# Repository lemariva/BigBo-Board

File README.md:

# BigBo-Board

BigBo is a multi-target board for Energy Metering & Power Monitoring. It's the big brother of [PiCoBo](https://github.com/lemariva/PiCoBo-Board). I designed it using the MSP430F5529LP that is part of the MSP430 Texas Instruments family of low-power microcontrollers.

More info will be available on https://lemariva.com soon.

## Components
The board includes:
* CP2102 for UART communication (with ESD-Protection)
* Socket for a NRF24L01 module
* CD4504B: level shifter
* BQ27510-Q3: battery fuel gauge
* BQ24210DQCT: Li-Ion battery charger
* CAT24FC32UI: EEPROM memory
* TPS6300x: buck-boost converters (for 5V)
* MCP39F501: power-monitoring
* etc.

This board is a Energy Metering & Power Monitoring demonstration board with communication possibilities (0.1% error across 4000:1 dynamic range). I designed it near 2013, when home solutions were limited and expensive. The power energy metering & power monitoring functions are based on the [ARD00455](https://www.microchip.com/Developmenttools/ProductDetails/ARD00455) board.

The board can be supplied using:
* a battery (Li-Ion) which can be also charged
* 5V over the micro-usb connector
* 230V AC (not a typo error - 230V AC!). The floating 3.3V is generated using a LM1117. Check the HIGH-Voltage page on the schematic.

Additionally multiple pinouts are available to connect external sensors (e.g. DHT11), servo motors, LEDs etc. For testing uses it can be programmed using the MSP430F5529LP LaunchPad.

## PCB
|||
|:- |:-|

### Applications
* Energy Metering & Power Monitoring
* Smart switch
* Sensor measurement (Temperature etc.)
* LEDs control
* Communication
* etc.

### Revision
* 1.0 first version

### Disclaimer
Use at your own risk and be careful specially with the 230V AC part.

I ordered the board (I have 10 PCBs over here) but I didn't have enough time to solder the components. I've checked the design many times but errors could be over there. I'll be updating the code that I had for the board soon.

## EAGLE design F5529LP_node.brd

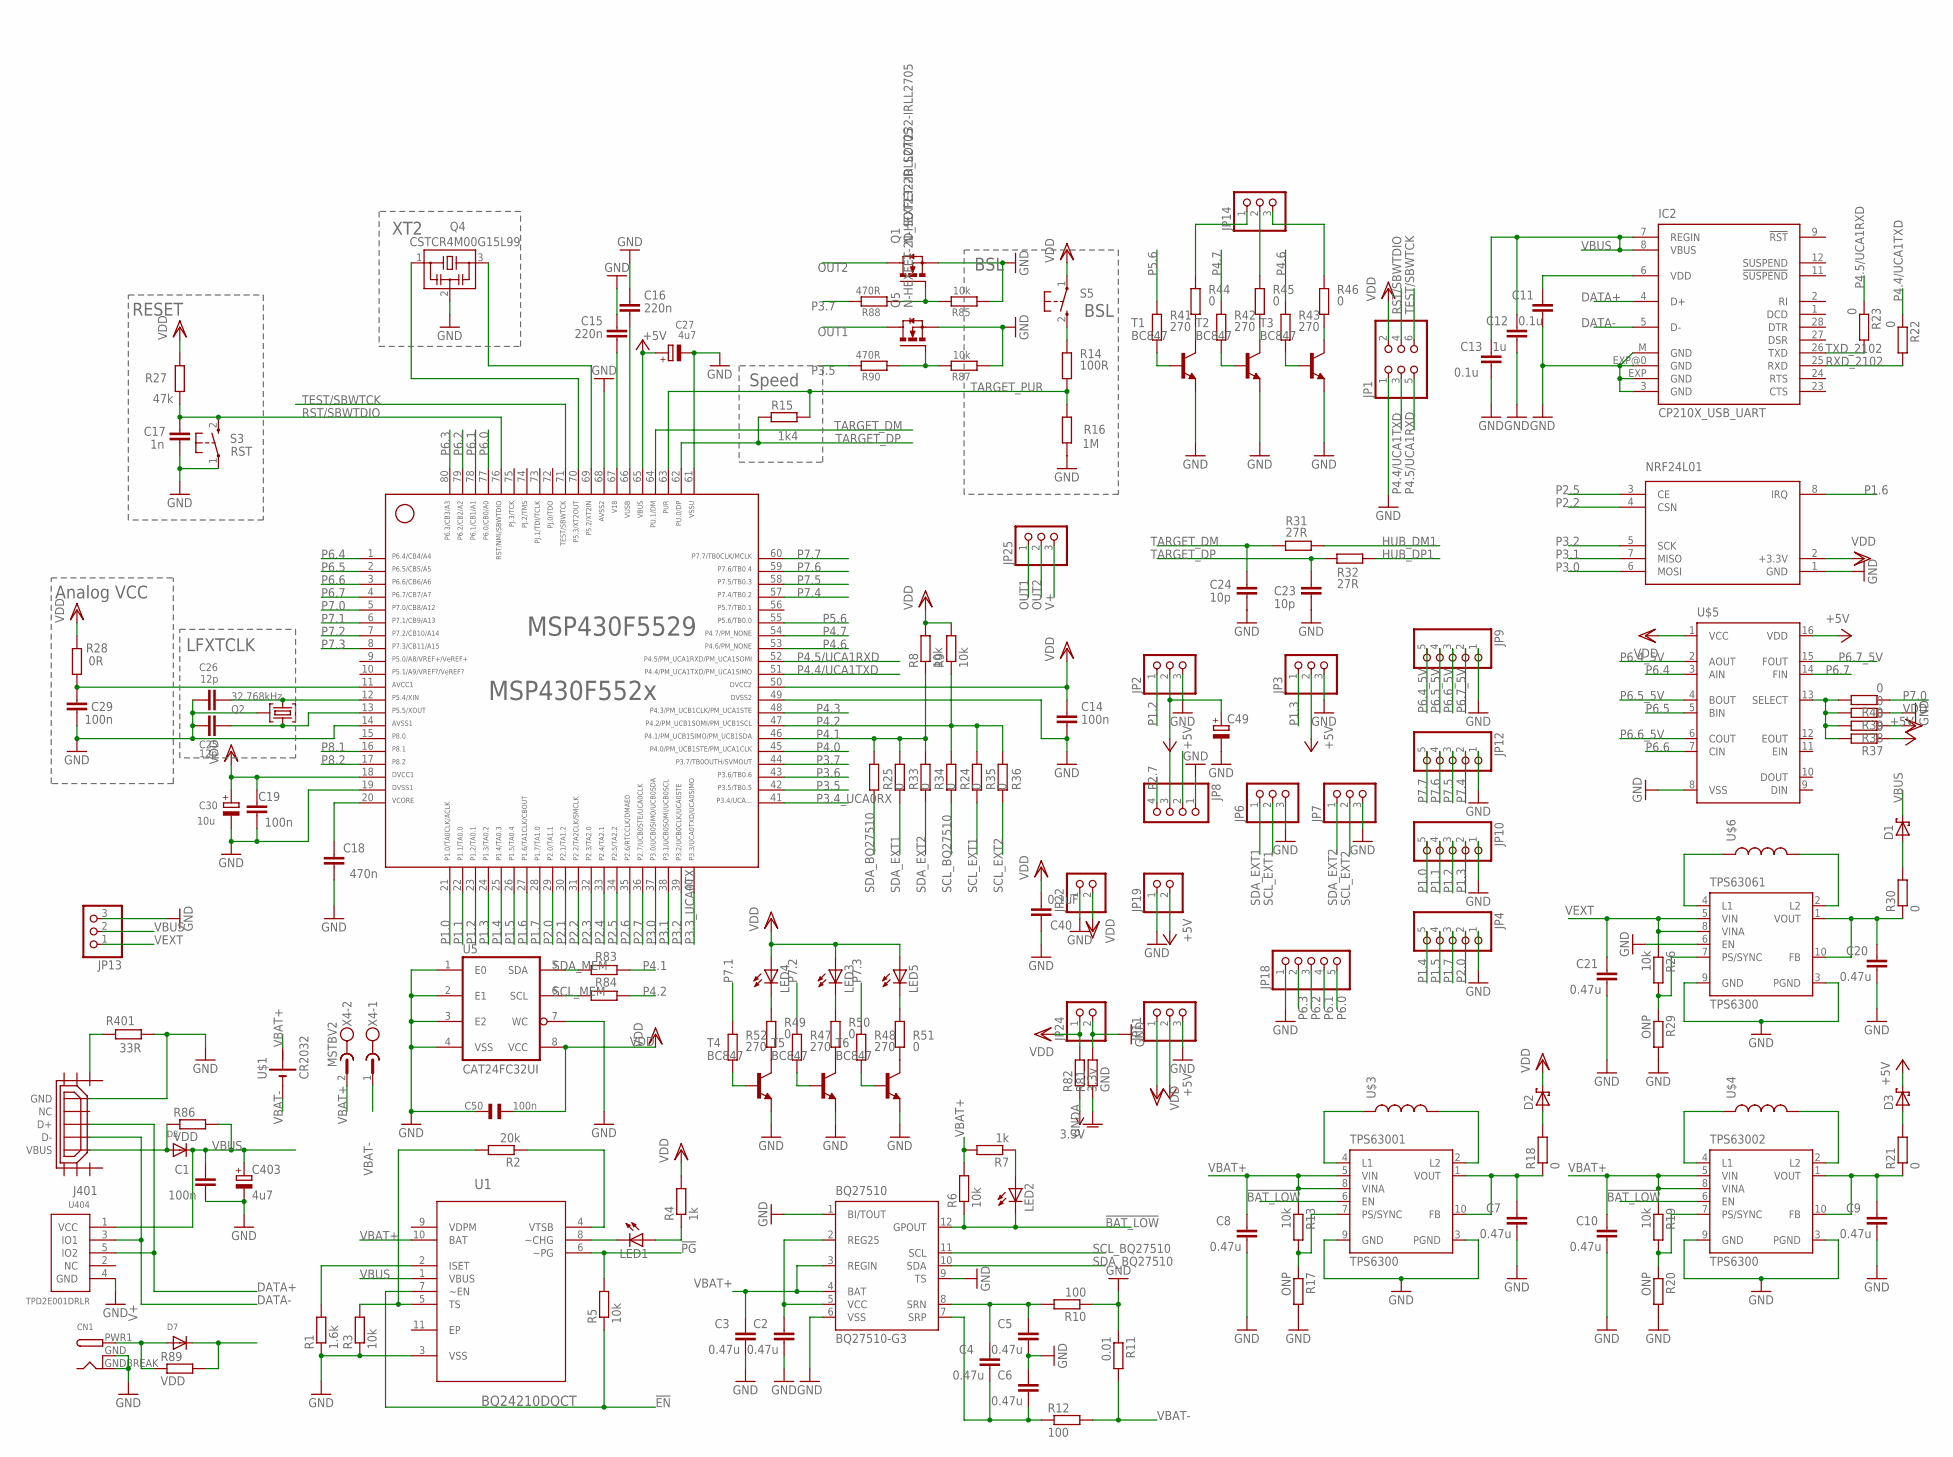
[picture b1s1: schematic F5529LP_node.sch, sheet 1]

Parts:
BQ27510: BQ27510-G3; DRZ
C1, C14, C19, C29: 100n; C0603
C2, C3, C4, C5, C6, C7, C8, C9, C10, C20, C21: 0.47u; C0603
C11, C13: 0.1u; C0603
C12: 1u; C0603
C15, C16: 220n; C0603
C17: 1n; C0603
C18: 470n; C0603
C23, C24: 10p; C0603
C25, C26: 12p; C0603
C27, C403: 4u7; A/3216-18R
C30: 10u; A/3216-18R
C40: 0.1uF; C0603
C49: CPOL-EUF; PANASONIC_F
C50: 100n; 0402
CN1: DCBARRELSMT; DCJACK_2MM_SMT
D1, D2, D3: SCHOTTKY-DIODE; DIODE_SMB
D7, D8: DIODESOT23_REFLOW; SOT23-R
IC2: CP210X_USB_UART; MLP28
J401: USB_MICRO_FLIPPED; HIROSE-ZX62R-B-5P
JP1: PINHD-2X3; 2X03
JP2, JP3, JP25: PINHD-1X3; 1X03
JP4, JP9, JP10, JP12, JP18: PINHD-1X5_2.00; 1X05M
JP6, JP7, JP11, JP13, JP14: PINHD-1X3_2.00; 1X03M
JP8: PINHD-1X4_2.00; 1X04M
JP19, JP22, JP24: PINHD-1X2_2.00; 1X02M
LED1, LED2, LED3, LED4, LED5: LEDSML0805; SML0805
MSP430F5529: MSP430F5529IPNR; PN80
NRF24L01: NRF24L01HP; NRF24L01_HP
Q1, Q5: N-HEXFET-2D_SOT232-IRLL2705; SOT223
Q2: 32.768kHz; MS3V-T1R
Q4: CSTCR4M00G15L99; MURATA-FILTER_CSTCR
R1: 1.6k; R0603
R2: 20k; R0603
R3, R5, R6, R8, R9, R13, R19, R26: 10k; R0603
R4, R7: 1k; R0603
R10, R12: 100; R0603
R11: 0.01; R0603
R14: 100R; R0603
R15: 1k4; R0603
R16: 1M; R0603
R17, R20, R29: ONP; R0603
R18, R21, R22, R23, R30, R37, R38, R39, R40, R44, R45, R46, R49, R50, R51: 0; R0603
R24, R25, R33, R34, R35, R36, R83, R84: 0; R0201
R27: 47k; R0603
R28: 0R; R0603
R31, R32: 27R; R0603
R41, R42, R43, R47, R48, R52: 270; R0603
R81: GND; R0402
R82: 3.3v; R0402
R85, R87: 10k; 0603
R86, R89: VDD; R0201
R88, R90: 470R; 0603
R401: 33R; R0603
S3: RST; PBTH
S5: BSL; PBTH
T1, T2, T3, T4, T5, T6: BC847; SOT23
TPS63001, TPS63002, TPS63061: TPS6300; DRC-S-PVSON-N10
U1: BQ24210DQCT; SON50P200X300X80-11N
U5: CAT24FC32UI; TSSOP8
U404: TPD2E001DRLR; TPD2E001-DRL
U$1: CR2032
U$3, U$4, U$6: INDUCTOR-B82462G; B82462G
U$5: CD4504B; SOIC16
X4: MSTBV2

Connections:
3.3V: R82.1; also elsewhere on the board
!BAT_LOW: BQ27510.12 (GPOUT), LED2.C, R6.1, TPS63001.6 (EN), TPS63002.6 (EN)
!EN: R5.1, U1.7 (~EN)
!PG: R5.2, U1.6 (~PG)
+5V: C27.+, C49.+, D3.C (A), JP2.2, JP3.2, JP11.2, JP19.2, MSP430F5529.65, R37.1, U$5.16 (VDD); also elsewhere on the board
AVCC: C29.1, MSP430F5529.11, R28.1
DATA+: IC2.4 (D+), J401.D+, U404.5 (IO2)
DATA-: IC2.5 (D-), J401.D-, U404.3 (IO1)
GND: BQ27510.1 (BI/TOUT), BQ27510.6 (VSS), BQ27510.9 (TS), C1.2, C2.2, C3.2, C5.2, C6.1, C7.2, C8.2, C9.2, C10.2, C11.2, C12.2, C13.2, C14.2, C15.2, C16.2, C17.2, C18.1, C19.1, C20.2, C21.2, C23.2, C24.2, C25.1, C26.1, C27.-, C29.2, C30.-, C40.1, C49.-, C50.2, C403.-, CN1.GND (GNDBREAK), CN1.GNDBREAK (GND), IC2.3 (GND), IC2.EXP (GND), IC2.EXP@0 (GND), IC2.M (GND), J401.GND, JP1.1, JP2.3, JP3.3, JP4.1, JP6.3, JP7.3, JP8.1, JP9.1, JP10.1, JP11.3, JP12.1, JP13.3, JP18.1, JP19.1, JP22.1, JP24.2, MSP430F5529.14, MSP430F5529.19, MSP430F5529.49, MSP430F5529.61, MSP430F5529.68, NRF24L01.1 (GND), Q1.3 (S), Q2.P3 (GND), Q4.2, Q5.3 (S), R1.1, R3.1, R10.1, R11.1, R16.1, R17.2, R20.2, R29.2, R39.1, R81.2, R85.1, R87.1, R401.2, S3.1, T1.2 (E), T2.2 (E), T3.2 (E), T4.2 (E), T5.2 (E), T6.2 (E), TPS63001.3 (PGND), TPS63001.9 (GND), TPS63002.3 (PGND), TPS63002.9 (GND), TPS63061.3 (PGND), TPS63061.6 (EN), TPS63061.9 (GND), U1.3 (VSS), U5.1 (E0), U5.2 (E1), U5.3 (E2), U5.4 (VSS), U5.7 (WC), U404.4 (GND), U$5.8 (VSS); also elsewhere on the board
GNDA: R81.1; also elsewhere on the board
HUB_DM1: R31.1
HUB_DP1: R32.1
unnamed: R1.2, U1.2 (ISET)
unnamed: R2.1, U1.4 (VTSB)
unnamed: R2.2, R3.2, U1.5 (TS)
unnamed: R14.1, S5.2 (S)
unnamed: LED1.C, U1.8 (~CHG)
unnamed: LED1.A, R4.1
unnamed: BQ27510.2 (REG25), BQ27510.5 (VCC), C2.1
unnamed: TPS63002.4 (L1), U$4.P$1 (1)
unnamed: LED2.A, R7.1
unnamed: J401.SHIELD1, R401.1
unnamed: BQ27510.8 (SRN), C4.1, C5.1, R10.2
unnamed: TPS63001.4 (L1), U$3.P$1 (1)
unnamed: TPS63001.2 (L2), U$3.P$2 (2)
unnamed: BQ27510.7 (SRP), C4.2, C6.2, R12.1
unnamed: TPS63002.2 (L2), U$4.P$2 (2)
unnamed: R13.2, R17.1, TPS63001.7 (PS/SYNC)
unnamed: R19.2, R20.1, TPS63002.7 (PS/SYNC)
unnamed: C9.1, R21.1, TPS63002.1 (VOUT), TPS63002.10 (FB)
unnamed: C7.1, R18.1, TPS63001.1 (VOUT), TPS63001.10 (FB)
unnamed: C11.1, IC2.6 (VDD)
unnamed: TPS63061.4 (L1), U$6.P$1 (1)
unnamed: TPS63061.2 (L2), U$6.P$2 (2)
unnamed: R26.2, R29.1, TPS63061.7 (PS/SYNC)
unnamed: C20.1, R30.1, TPS63061.1 (VOUT), TPS63061.10 (FB)
unnamed: R37.2, R38.2, R39.2, R40.2, U$5.13 (SELECT)
unnamed: R41.2, T1.1 (B)
unnamed: R42.2, T2.1 (B)
unnamed: R43.2, T3.1 (B)
unnamed: R46.2, T3.3 (C)
unnamed: JP14.1, R44.1
unnamed: JP14.2, R45.1
unnamed: JP14.3, R46.1
unnamed: R44.2, T1.3 (C)
unnamed: R45.2, T2.3 (C)
unnamed: D1.A (C), R30.2
unnamed: D2.A (C), R18.2
unnamed: D3.A (C), R21.2
unnamed: R47.2, T5.1 (B)
unnamed: R48.2, T6.1 (B)
unnamed: R51.2, T6.3 (C)
unnamed: LED4.C, R49.1
unnamed: LED3.C, R50.1
unnamed: LED5.C, R51.1
unnamed: R49.2, T4.3 (C)
unnamed: R50.2, T5.3 (C)
unnamed: R52.2, T4.1 (B)
unnamed: Q1.1 (G), R85.2, R88.1
unnamed: D8.1 (A), J401.VBUS, R86.1
unnamed: Q5.1 (G), R87.2, R90.1
OUT1: JP25.1, Q5.2 (D), Q5.4 (D)
OUT2: JP25.2, Q1.2 (D), Q1.4 (D)
P1.0: JP10.5, MSP430F5529.21
P1.1: JP10.4, MSP430F5529.22
P1.2: JP2.1, JP10.3, MSP430F5529.23
P1.3: JP3.1, JP10.2, MSP430F5529.24
P1.4: JP4.5, MSP430F5529.25
P1.5: JP4.4, MSP430F5529.26
P1.6: MSP430F5529.27, NRF24L01.8 (IRQ)
P1.7: JP4.3, MSP430F5529.28
P2.0: JP4.2, MSP430F5529.29
P2.1: MSP430F5529.30
P2.2: MSP430F5529.31, NRF24L01.4 (CSN)
P2.3: MSP430F5529.32
P2.4: MSP430F5529.33
P2.5: MSP430F5529.34, NRF24L01.3 (CE)
P2.6: MSP430F5529.35
P2.7: JP8.4, MSP430F5529.36; also elsewhere on the board
P3.0: MSP430F5529.37, NRF24L01.6 (MOSI)
P3.1: MSP430F5529.38, NRF24L01.7 (MISO)
P3.2: MSP430F5529.39, NRF24L01.5 (SCK)
P3.3_UCA0TX: JP8.2, MSP430F5529.40; also elsewhere on the board
P3.4_UCA0RX: JP8.3, MSP430F5529.41; also elsewhere on the board
P3.5: MSP430F5529.42, R90.2
P3.6: MSP430F5529.43
P3.7: MSP430F5529.44, R88.2
P4.0: MSP430F5529.45
P4.1: MSP430F5529.46, R8.1, R25.1, R33.1, R34.1, R83.2
P4.2: MSP430F5529.47, R9.1, R24.1, R35.1, R36.1, R84.2
P4.3: MSP430F5529.48
P4.4/UCA1TXD: JP1.3, MSP430F5529.51, R22.1
P4.5/UCA1RXD: JP1.5, MSP430F5529.52, R23.1
P4.6: MSP430F5529.53, R43.1
P4.7: MSP430F5529.54, R42.1
P5.2/XT2IN: MSP430F5529.69, Q4.3
P5.3/XT2OUT: MSP430F5529.70, Q4.1
P5.4/XIN: C26.2, MSP430F5529.12, Q2.P2 (2)
P5.5/XOUT: C25.2, MSP430F5529.13, Q2.P1 (1)
P5.6: MSP430F5529.55, R41.1
P6.0: JP18.5, MSP430F5529.77
P6.1: JP18.4, MSP430F5529.78
P6.2: JP18.3, MSP430F5529.79
P6.3: JP18.2, MSP430F5529.80
P6.4: MSP430F5529.1, U$5.3 (AIN)
P6.4_5V: JP9.5, U$5.2 (AOUT)
P6.5: MSP430F5529.2, U$5.5 (BIN)
P6.5_5V: JP9.4, U$5.4 (BOUT)
P6.6: MSP430F5529.3, U$5.7 (CIN)
P6.6_5V: JP9.3, U$5.6 (COUT)
P6.7: MSP430F5529.4, U$5.14 (FIN)
P6.7_5V: JP9.2, U$5.15 (FOUT)
P7.0: MSP430F5529.5, R40.1
P7.1: MSP430F5529.6, R52.1
P7.2: MSP430F5529.7, R47.1
P7.3: MSP430F5529.8, R48.1
P7.4: JP12.2, MSP430F5529.57
P7.5: JP12.3, MSP430F5529.58
P7.6: JP12.4, MSP430F5529.59
P7.7: JP12.5, MSP430F5529.60
P8.1: MSP430F5529.16
P8.2: MSP430F5529.17
PWPD: BQ27510.EXP@1 (PWPD), BQ27510.EXP@2 (PWPD), BQ27510.EXP@3 (PWPD), BQ27510.EXP@4 (PWPD), BQ27510.EXP@5 (PWPD), BQ27510.EXP@6 (PWPD), BQ27510.EXP@7 (PWPD), BQ27510.EXP@8 (PWPD), BQ27510.EXP@9 (PWPD)
RST/SBWTDIO: C17.1, JP1.4, MSP430F5529.76, R27.1, S3.2 (S)
RXD_2102: IC2.25 (RXD), R22.2
SCL_BQ27510: BQ27510.11 (SCL), R24.2
SCL_EXT1: JP6.2, R35.2
SCL_EXT2: JP7.2, R36.2
SCL_MEM: R84.1, U5.6 (SCL)
SDA_BQ27510: BQ27510.10 (SDA), R25.2
SDA_EXT1: JP6.1, R33.2
SDA_EXT2: JP7.1, R34.2
SDA_MEM: R83.1, U5.5 (SDA)
TARGET_DM: C24.1, MSP430F5529.64, R31.2
TARGET_DP: C23.1, MSP430F5529.62, R15.2, R32.2
TARGET_PUR: MSP430F5529.63, R14.2, R15.1, R16.2
TARGET_VUSB: C16.1, MSP430F5529.66
TEST/SBWTCK: JP1.6, MSP430F5529.71
TXD_2102: IC2.26 (TXD), R23.2
V18: C15.1, MSP430F5529.67
V+: CN1.PWR1 (PWR), D7.1 (A), JP25.3, R89.1
VBAT+: BQ27510.3 (REGIN), BQ27510.4 (BAT), C3.1, C8.1, C10.1, R6.2, R7.2, R13.1, R19.1, TPS63001.5 (VIN), TPS63001.8 (VINA), TPS63002.5 (VIN), TPS63002.8 (VINA), U1.10 (BAT), U$1.P$1 (+), X4.2
VBAT-: R11.2, R12.2, U$1.P$2 (-), X4.1
VBUS: C1.1, C12.1, C13.1, C403.+, D1.C (A), D7.3 (C), D8.3 (C), IC2.7 (REGIN), IC2.8 (VBUS), JP13.2, R86.2, R89.2, U1.1 (VBUS), U404.1 (VCC)
VCORE: C18.2, MSP430F5529.20
VDD: C14.1, C19.2, C30.+, C40.2, C50.1, D2.C (A), JP1.2, JP11.1, JP22.2, JP24.1, LED3.A, LED4.A, LED5.A, MSP430F5529.18, MSP430F5529.50, NRF24L01.2 (+3.3V), R4.2, R8.2, R9.2, R27.2, R28.2, R38.1, R82.2, S5.1, U5.8 (VCC), U$5.1 (VCC); also elsewhere on the board
VEXT: C21.1, JP13.1, R26.1, TPS63061.5 (VIN), TPS63061.8 (VINA)

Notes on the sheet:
RESET
LFXTCLK
XT2
BSL
Speed
Analog VCC

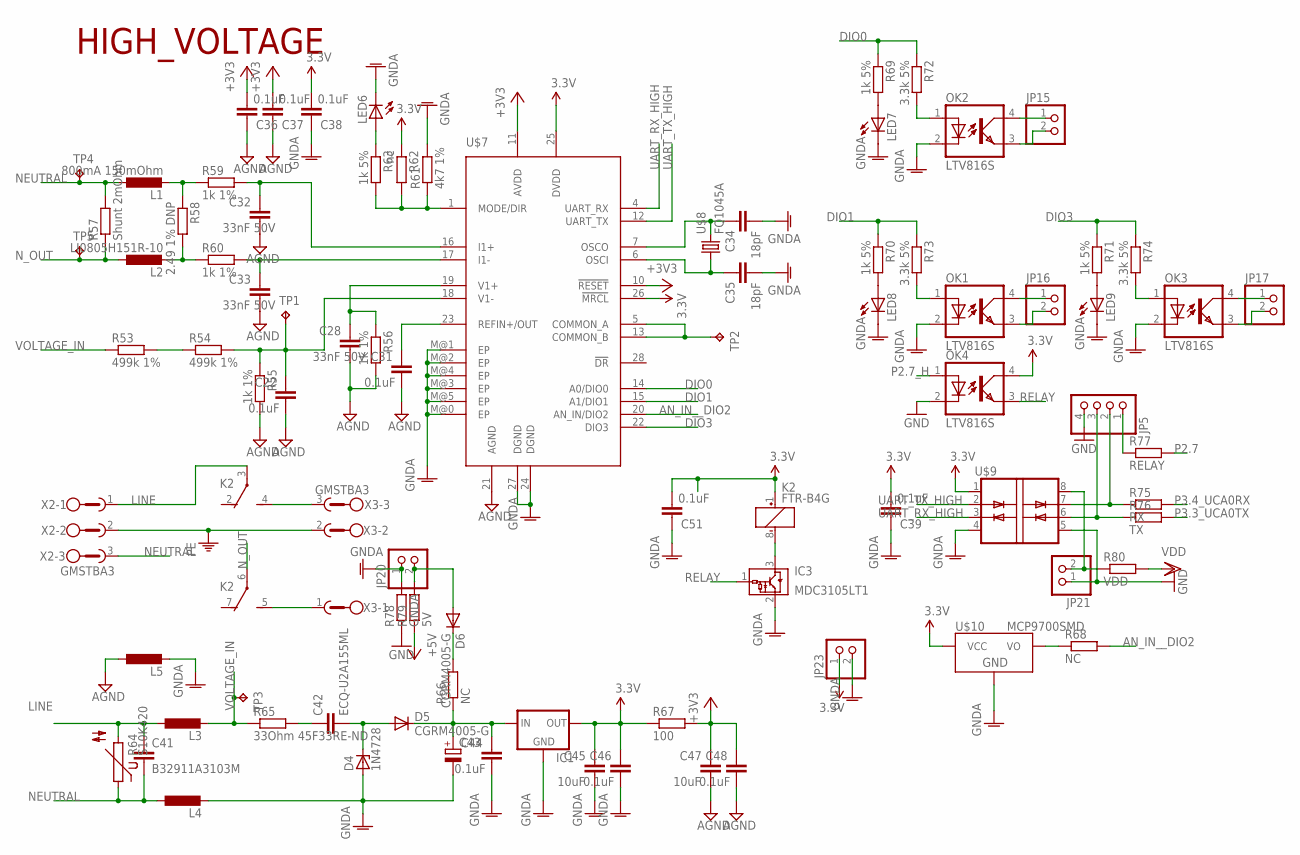
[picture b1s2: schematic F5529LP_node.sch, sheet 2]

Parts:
C22, C31, C36, C37, C38, C39, C44, C46, C48: 0.1uF; C0603
C28, C32, C33: 33nF 50V; C0603
C34, C35: 18pF; C0603
C41: B32911A3103M; C075-042X103
C42: ECQ-U2A155ML; C275-173X316
C43: CPOL-EUF; PANASONIC_F
C45, C47: 10uF; C1206
C51: 0.1uF; C0805
D4: 1N4728; DO41Z10
D5, D6: CGRM4005-G; SOD-123_MINI-SMA
IC1: LM1117; SOT223
IC3: MDC3105LT1; SOT23
JP5: PINHD-1X4_2.00; 1X04M
JP15, JP16, JP17, JP20, JP21, JP23: PINHD-1X2_2.00; 1X02M
K2: FTR-B4G
L1: 800mA 150mOhm; L2825P
L2: LI0805H151R-10; L2825P
L3, L4: L-EU0207/5V; 0207/5V
L5: L-EUL2825P; L2825P
LED6, LED7, LED8, LED9: LEDCHIPLED_0805; CHIPLED_0805
OK1, OK2, OK3, OK4: LTV816S; SMD4
R53, R54: 499k 1%; R2010
R55, R56, R59, R60: 1k 1%; R0603
R57: Shunt 2mOhm; R2512
R58: 2.49 1% DNP; R0603
R61: 4k7 1%; R0603
R62: nc; R0603
R63, R69, R70, R71: 1k 5%; R0603
R64: S10K420
R65: 33Ohm 45F33RE-ND; 0617V
R66: NC; R2010
R67: 100; R0603
R68: NC; R0603
R72, R73, R74: 3.3k 5%; R0603
R75: RX; R0201
R76: TX; R0201
R77: RELAY; R0201
R78: GNDA; R0402
R79: 5V; R0402
R80: VDD; R0201
TP1, TP3, TP4, TP5: TPB2,54; B2,54
TP2: TPB1,27; B1,27
U$7: MCP39F501; QFN28
U$8: FQ1045A
U$9: IL712; SOIC08
U$10: MCP9700SMD; SOT23-3
U$11: HIGH_VOLTAGE
X2, X3: GMSTBA3

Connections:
3.3V: C38.2, C39.2, C45.1, C46.1, C51.2, IC1.2 (OUT), JP23.1, K2.1 (+), OK4.4 (COL), R62.1, R67.1, U$7.25 (DVDD), U$7.26 (!MRCL), U$9.1 (VDD1), U$10.1 (VCC); also elsewhere on the board
!DR: U$7.28 (!DR)
+3V3: C36.2, C37.2, C47.1, C48.1, R67.2, U$7.10 (!RESET), U$7.11 (AVDD)
+5V: R79.1; also elsewhere on the board
AGND: C22.2, C28.2, C31.2, C32.2, C33.2, C36.1, C37.1, C47.2, C48.2, L5.1, R55.2, R56.2, U$7.21 (AGND)
AN_IN__DIO2: R68.2, U$7.20 (AN_IN/DIO2)
DIO0: R69.1, R72.1, U$7.14 (A0/DIO0)
DIO1: R70.1, R73.1, U$7.15 (A1/DIO1)
DIO3: R71.1, R74.1, U$7.22 (DIO3)
GND: JP5.4, JP21.1, OK4.2 (C), R78.1, U$9.5 (GND2); also elsewhere on the board
GNDA: C34.2, C35.2, C38.1, C39.1, C43.-, C44.2, C45.2, C46.2, C51.1, D4.A, IC1.1 (GND), IC3.2 (GND), JP20.1, JP23.2, L4.2, L5.2, LED6.C, LED7.C, LED8.C, LED9.C, OK1.2 (C), OK2.2 (C), OK3.2 (C), R61.2, R78.2, U$7.24 (DGND), U$7.27 (DGND), U$7.M@0 (EP), U$7.M@1 (EP), U$7.M@2 (EP), U$7.M@3 (EP), U$7.M@4 (EP), U$7.M@5 (EP), U$9.4 (GND1), U$10.3 (GND); also elsewhere on the board
LINE: C41.1, K2.3, L3.1, R64.2, X2.1
LINE_RELAY: K2.4 (S), X3.3
unnamed: LED8.A, R70.2
unnamed: R53.2, R54.1
unnamed: C22.1, R54.2, R55.1, TP1.TP, U$7.18 (V1-)
unnamed: C28.1, R56.1, U$7.19 (V1+)
unnamed: C31.1, U$7.23 (REFIN+/OUT)
unnamed: LED7.A, R69.2
unnamed: LED9.A, R71.2
unnamed: L1.2, R58.1, R59.1
unnamed: L2.2, R58.2, R60.1
unnamed: C33.1, R60.2, U$7.17 (I1-)
unnamed: C32.1, R59.2, U$7.16 (I1+)
unnamed: R61.1, R62.2, R63.2, U$7.1 (MODE/DIR)
unnamed: LED6.A, R63.1
unnamed: C34.1, U$7.7 (OSCO), U$8.2 (3)
unnamed: C35.1, U$7.6 (OSCI), U$8.1
unnamed: C43.+, C44.1, D5.C, IC1.3 (IN), R66.1
unnamed: D6.C, R66.2
unnamed: OK2.1 (A), R72.2
unnamed: TP2.TP, U$7.5 (COMMON_A), U$7.13 (COMMON_B)
unnamed: R68.1, U$10.2 (VO)
unnamed: C42.2, D4.C, D5.A
unnamed: C42.1, R65.2
unnamed: OK1.1 (A), R73.2
unnamed: OK3.1 (A), R74.2
unnamed: JP5.2, R75.1, U$9.7 (OUT1)
unnamed: JP5.3, R76.1, U$9.6 (IN2)
unnamed: JP15.1, OK2.4 (COL)
unnamed: JP15.2, OK2.3 (EMIT)
unnamed: JP16.1, OK1.4 (COL)
unnamed: JP16.2, OK1.3 (EMIT)
unnamed: JP17.1, OK3.4 (COL)
unnamed: JP17.2, OK3.3 (EMIT)
unnamed: IC3.3 (VOUT), K2.8 (-)
unnamed: D6.A, JP20.2, R79.2
unnamed: JP21.2, R80.1, U$9.8 (VDD2)
NEUTRAL: C41.2, L1.1, L4.1, R57.2, R64.1, TP4.TP, X2.3
NEUTRAL_RELAY: K2.5 (S), X3.1
N_OUT: K2.6, L2.1, R57.1, TP5.TP
P2.7: R77.2; also elsewhere on the board
P2.7_H: JP5.1, OK4.1 (A), R77.1
P3.3_UCA0TX: R76.2; also elsewhere on the board
P3.4_UCA0RX: R75.2; also elsewhere on the board
PE: X2.2, X3.2
RELAY: IC3.1 (VIN), OK4.3 (EMIT)
UART_RX_HIGH: U$7.4 (UART_RX), U$9.3 (OUT2)
UART_TX_HIGH: U$7.12 (UART_TX), U$9.2 (IN1)
VDD: R80.2; also elsewhere on the board
VOLTAGE_IN: L3.2, R53.1, R65.1, TP3.TP

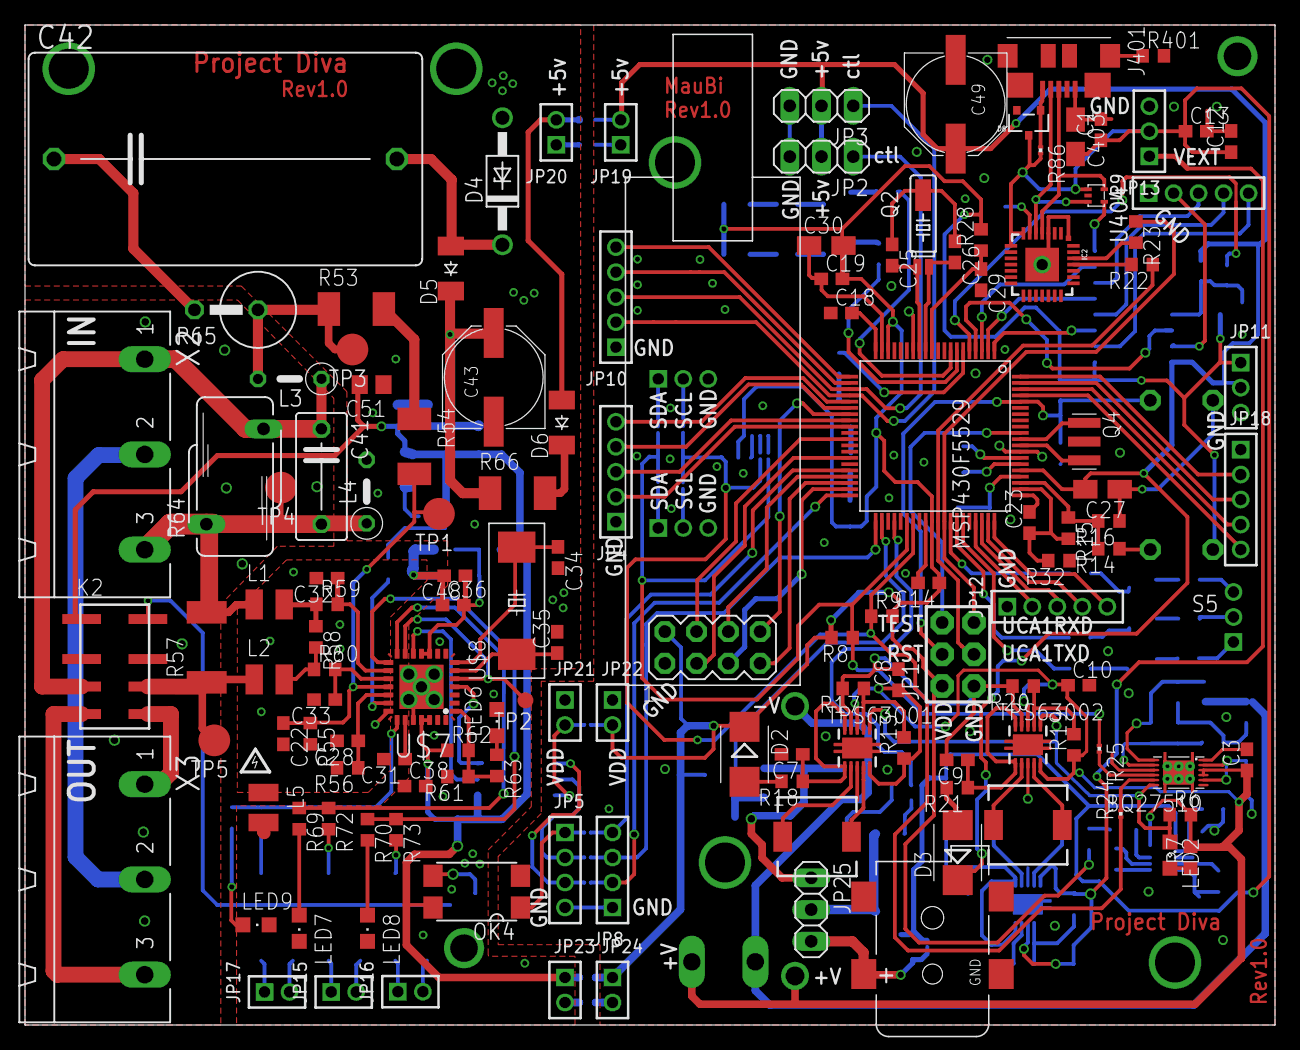
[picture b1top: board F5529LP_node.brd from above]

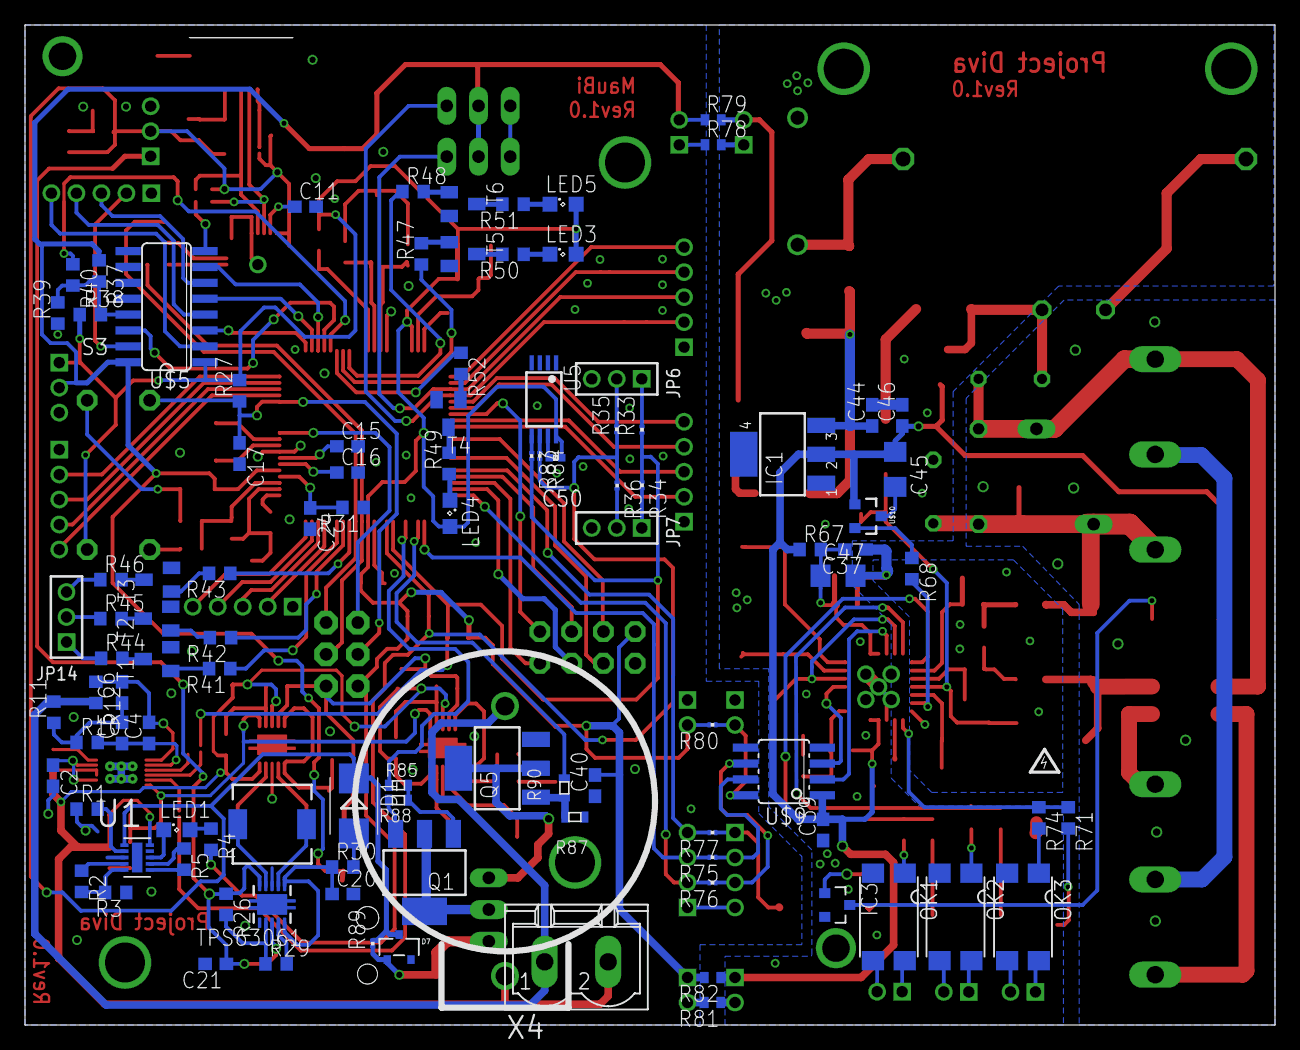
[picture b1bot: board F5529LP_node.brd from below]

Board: 2 copper layers, 100.0 x 80.0 mm, 240 parts (104 on the bottom side), 188 nets.

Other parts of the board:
U$12: HIGH_VOLTAGE

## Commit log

2018-10-07 added link to https://lemariva.com
2018-10-07 uploaded PCB bottom and top side pictures
2018-10-07 pictures resized
2018-10-07 move pics to a table
